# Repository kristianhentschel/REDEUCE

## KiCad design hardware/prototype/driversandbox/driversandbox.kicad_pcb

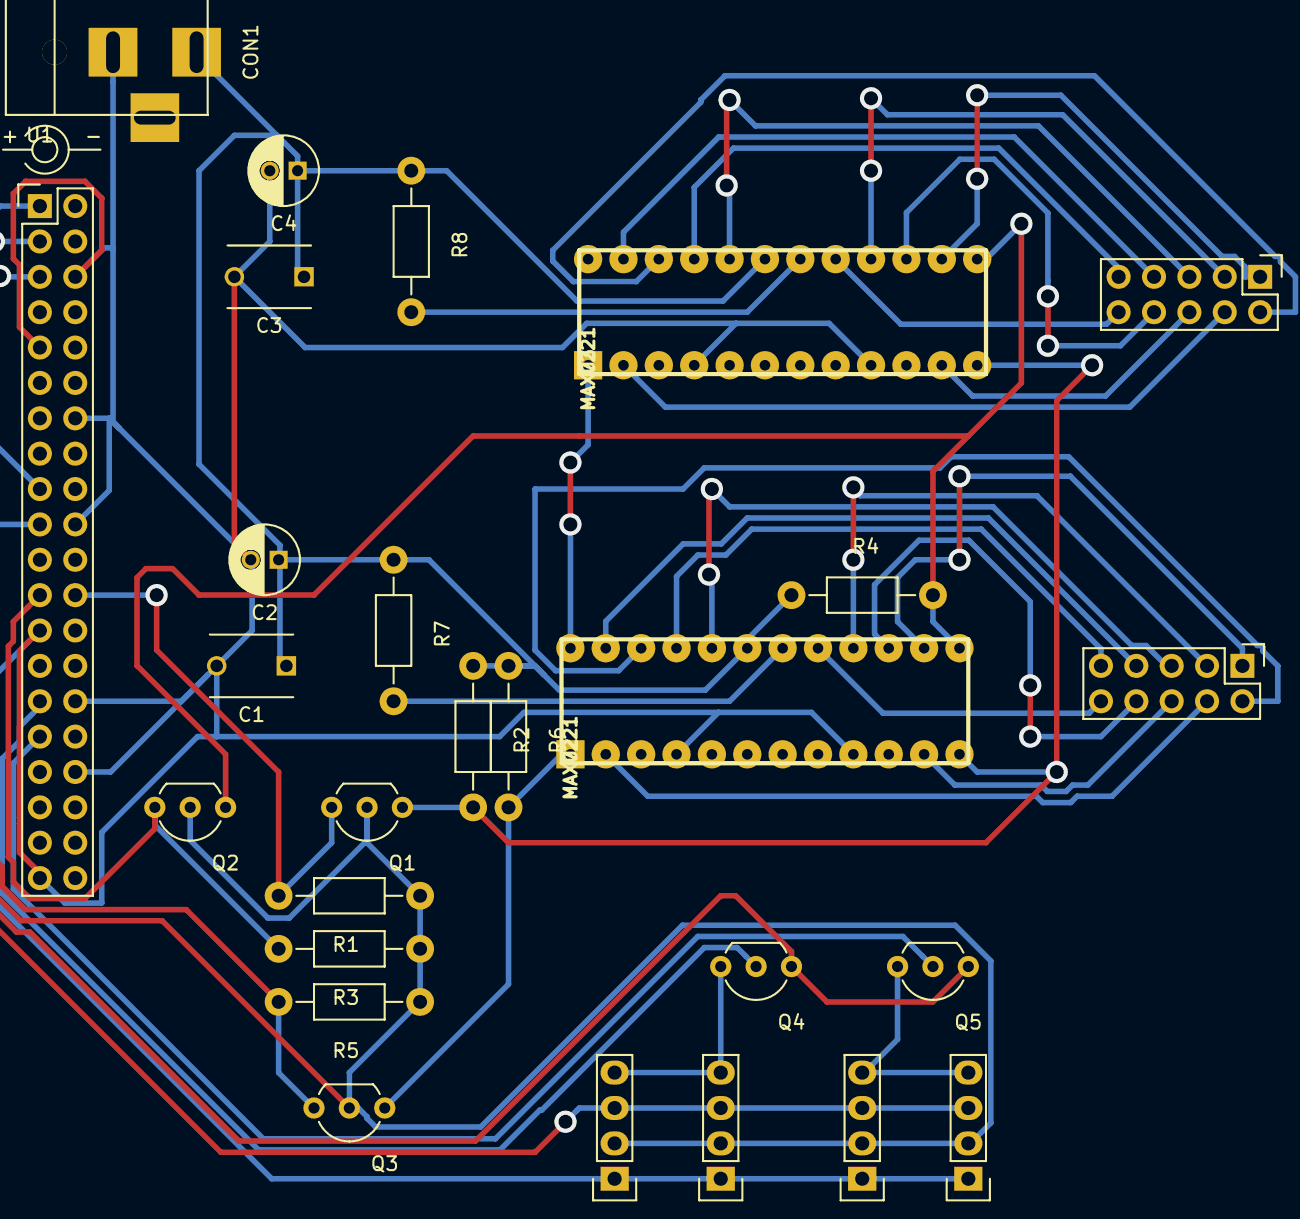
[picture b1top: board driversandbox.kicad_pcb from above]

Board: 2 copper layers, 27 parts (0 on the bottom side), 38 nets.

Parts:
C1, C3: C; C_Disc_D6_P5
C2, C4: CP; C_Radial_D5_L11_P2
CON1: BARREL_JACK; BARREL_JACK-custom
P1, P2, P3, P4: CONN_01X04; Pin_Header_Straight_1x04
P20, P24: CONN_02X05; Pin_Header_Straight_2x05
Q1, Q2, Q3, Q4, Q5: 2N7000; TO-92_Inline_Wide
R1, R2, R3, R4, R5, R6: 10K; Resistor_Horizontal_RM10mm
R7, R8: R_SET; Resistor_Horizontal_RM10mm
U1: Pi2_Connector; Pin_Header_Straight_2x20
U2, U3: MAX7221; DIL24

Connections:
/EN_I2C0_1: Q4.2, U1.29
/EN_I2C0_2: Q5.2, U1.31
/I2C1_SCL: Q4.1, Q5.1, U1.5
/I2C1_SDA: P1.3, P2.3, P3.3, P4.3, U1.3
/sheet57A5CF13/CLK_5V: Q2.1, R4.2, U2.13, U3.13
/sheet57A5CF13/DIG0: P20.4, U2.2
/sheet57A5CF13/DIG1: P20.6, U2.11
/sheet57A5CF13/SEGA: P20.1, U2.14
/sheet57A5CF13/SEGB: P20.3, U2.16
/sheet57A5CF13/SEGC: P20.5, U2.20
/sheet57A5CF13/SEGD: P20.7, U2.23
/sheet57A5CF13/SEGDP: P20.2, U2.22
/sheet57A5CF13/SEGE: P20.9, U2.21
/sheet57A5CF13/SEGF: P20.8, U2.15
/sheet57A5CF13/SEGG: P20.10, U2.17
/sheet57A5D898/DIG0: P24.4, U3.2
/sheet57A5D898/DIG1: P24.6, U3.11
/sheet57A5D898/DIN_5V: U2.24, U3.1
/sheet57A5D898/SEGA: P24.1, U3.14
/sheet57A5D898/SEGB: P24.3, U3.16
/sheet57A5D898/SEGC: P24.5, U3.20
/sheet57A5D898/SEGD: P24.7, U3.23
/sheet57A5D898/SEGDP: P24.2, U3.22
/sheet57A5D898/SEGE: P24.9, U3.21
/sheet57A5D898/SEGF: P24.8, U3.15
/sheet57A5D898/SEGG: P24.10, U3.17
/sheet57A33FA6/CMOS_OUT: Q1.1, R2.2, U2.12, U3.12
/sheet57A33FA6/TTL_IN: Q1.3, R1.2, U1.24
/sheet57A33FA7/TTL_IN: Q2.3, R3.2, U1.23
/sheet57A33FA8/CMOS_OUT: Q3.1, R6.2, U2.1
/sheet57A33FA8/TTL_IN: Q3.3, R5.2, U1.19
GND: C1.2, C2.2, C3.2, C4.2, CON1.2, P1.1, P2.1, P3.1, P4.1, U1.6, U1.9, U1.14, U1.20, U1.25, U1.30, U1.34, U1.39, U2.4, U2.9, U3.4, U3.9
unnamed: P1.4, P3.4, Q4.3
unnamed: P2.4, P4.4, Q5.3
unnamed: R7.2, U2.18
unnamed: R8.2, U3.18
VCC: C1.1, C2.1, C3.1, C4.1, CON1.1, R2.1, R4.1, R6.1, R7.1, R8.1, U2.19, U3.19
VDD: P1.2, P2.2, P3.2, P4.2, Q1.2, Q2.2, Q3.2, R1.1, R3.1, R5.1, U1.1, U1.17

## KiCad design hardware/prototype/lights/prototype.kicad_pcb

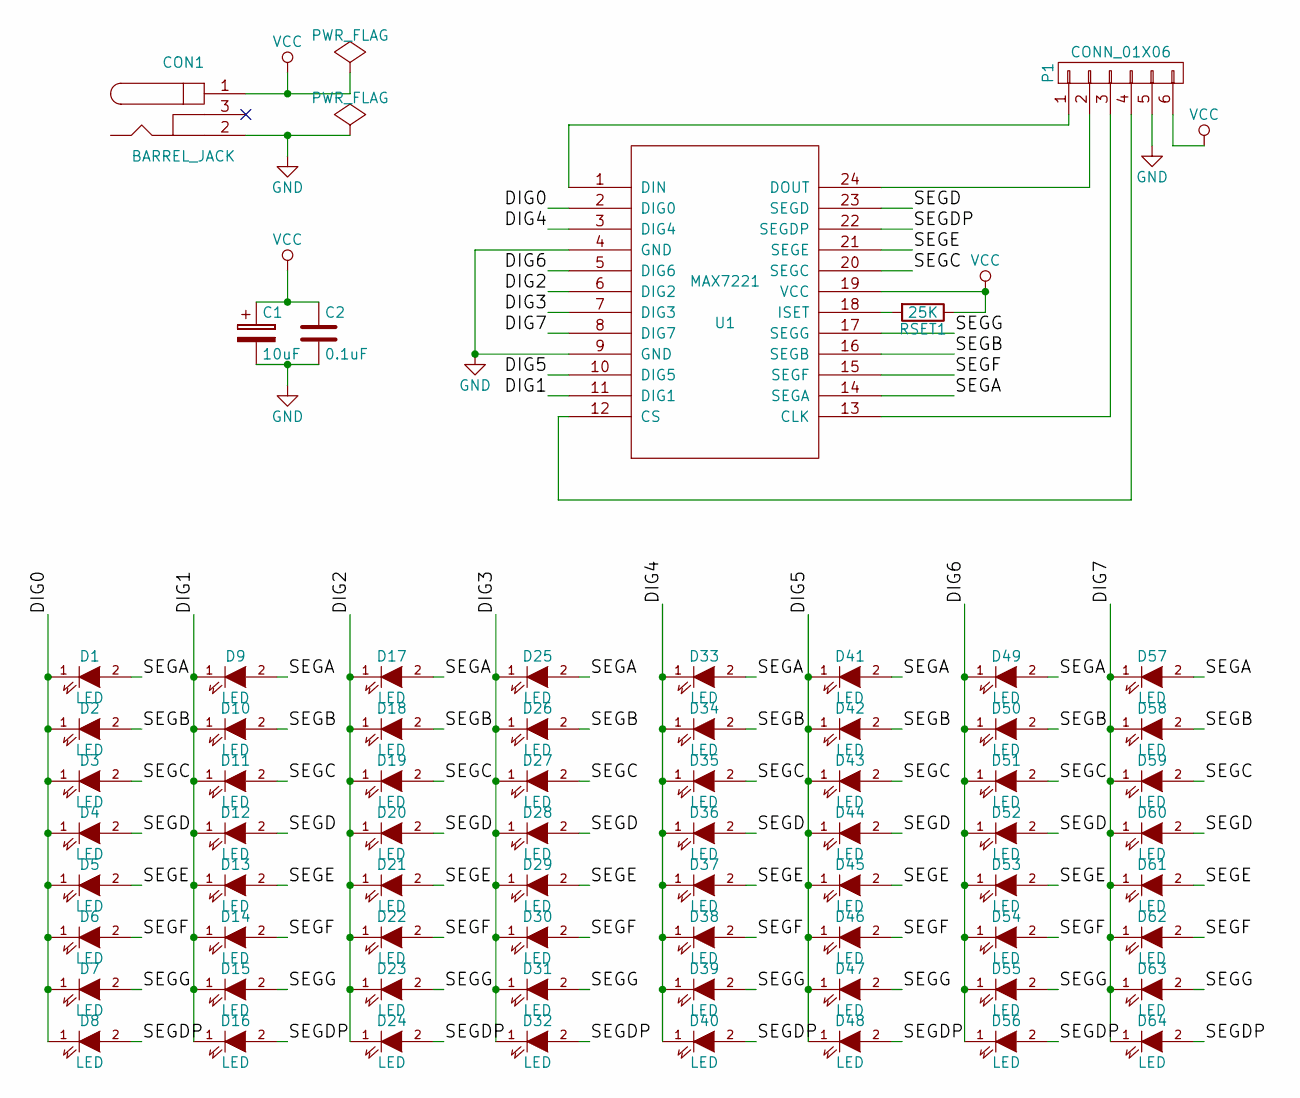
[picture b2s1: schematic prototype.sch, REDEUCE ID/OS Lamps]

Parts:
C1: 10uF
C2: 0.1uF
CON1: BARREL_JACK
D1, D2, D3, D4, D5, D6, D7, D8, D9, D10, D11, D12, D13, D14, D15, D16, D17, D18, D19, D20, D21, D22, D23, D24, D25, D26, D27, D28, D29, D30, D31, D32, D33, D34, D35, D36, D37, D38, D39, D40, D41, D42, D43, D44, D45, D46, D47, D48, D49, D50, D51, D52, D53, D54, D55, D56, D57, D58, D59, D60, D61, D62, D63, D64: LED; LED-5MM
P1: CONN_01X06; Pin_Header_Angled_1x06
RSET1: 25K; Resistor_Horizontal_RM10mm
U1: MAX7221; DIL24

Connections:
/DIG0: D1.1 (K), D2.1 (K), D3.1 (K), D4.1 (K), D5.1 (K), D6.1 (K), D7.1 (K), D8.1 (K), U1.2 (DIG0)
/DIG1: D9.1 (K), D10.1 (K), D11.1 (K), D12.1 (K), D13.1 (K), D14.1 (K), D15.1 (K), D16.1 (K), U1.11 (DIG1)
/DIG2: D17.1 (K), D18.1 (K), D19.1 (K), D20.1 (K), D21.1 (K), D22.1 (K), D23.1 (K), D24.1 (K), U1.6 (DIG2)
/DIG3: D25.1 (K), D26.1 (K), D27.1 (K), D28.1 (K), D29.1 (K), D30.1 (K), D31.1 (K), D32.1 (K), U1.7 (DIG3)
/DIG4: D33.1 (K), D34.1 (K), D35.1 (K), D36.1 (K), D37.1 (K), D38.1 (K), D39.1 (K), D40.1 (K), U1.3 (DIG4)
/DIG5: D41.1 (K), D42.1 (K), D43.1 (K), D44.1 (K), D45.1 (K), D46.1 (K), D47.1 (K), D48.1 (K), U1.10 (DIG5)
/DIG6: D49.1 (K), D50.1 (K), D51.1 (K), D52.1 (K), D53.1 (K), D54.1 (K), D55.1 (K), D56.1 (K), U1.5 (DIG6)
/DIG7: D57.1 (K), D58.1 (K), D59.1 (K), D60.1 (K), D61.1 (K), D62.1 (K), D63.1 (K), D64.1 (K), U1.8 (DIG7)
/SEGA: D1.2 (A), D9.2 (A), D17.2 (A), D25.2 (A), D33.2 (A), D41.2 (A), D49.2 (A), D57.2 (A), U1.14 (SEGA)
/SEGB: D2.2 (A), D10.2 (A), D18.2 (A), D26.2 (A), D34.2 (A), D42.2 (A), D50.2 (A), D58.2 (A), U1.16 (SEGB)
/SEGC: D3.2 (A), D11.2 (A), D19.2 (A), D27.2 (A), D35.2 (A), D43.2 (A), D51.2 (A), D59.2 (A), U1.20 (SEGC)
/SEGD: D4.2 (A), D12.2 (A), D20.2 (A), D28.2 (A), D36.2 (A), D44.2 (A), D52.2 (A), D60.2 (A), U1.23 (SEGD)
/SEGDP: D8.2 (A), D16.2 (A), D24.2 (A), D32.2 (A), D40.2 (A), D48.2 (A), D56.2 (A), D64.2 (A), U1.22 (SEGDP)
/SEGE: D5.2 (A), D13.2 (A), D21.2 (A), D29.2 (A), D37.2 (A), D45.2 (A), D53.2 (A), D61.2 (A), U1.21 (SEGE)
/SEGF: D6.2 (A), D14.2 (A), D22.2 (A), D30.2 (A), D38.2 (A), D46.2 (A), D54.2 (A), D62.2 (A), U1.15 (SEGF)
/SEGG: D7.2 (A), D15.2 (A), D23.2 (A), D31.2 (A), D39.2 (A), D47.2 (A), D55.2 (A), D63.2 (A), U1.17 (SEGG)
GND: C1.2, C2.2, CON1.2, P1.5, U1.4 (GND), U1.9 (GND)
unnamed: P1.1, U1.1 (DIN)
unnamed: P1.2, U1.24 (DOUT)
unnamed: P1.3, U1.13 (CLK)
unnamed: P1.4, U1.12 (CS)
unnamed: RSET1.2, U1.18 (ISET)
VCC: C1.1, C2.1, CON1.1, P1.6, RSET1.1, U1.19 (VCC)

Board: 2 copper layers, 68 parts (0 on the bottom side), 23 nets, no tracks yet.

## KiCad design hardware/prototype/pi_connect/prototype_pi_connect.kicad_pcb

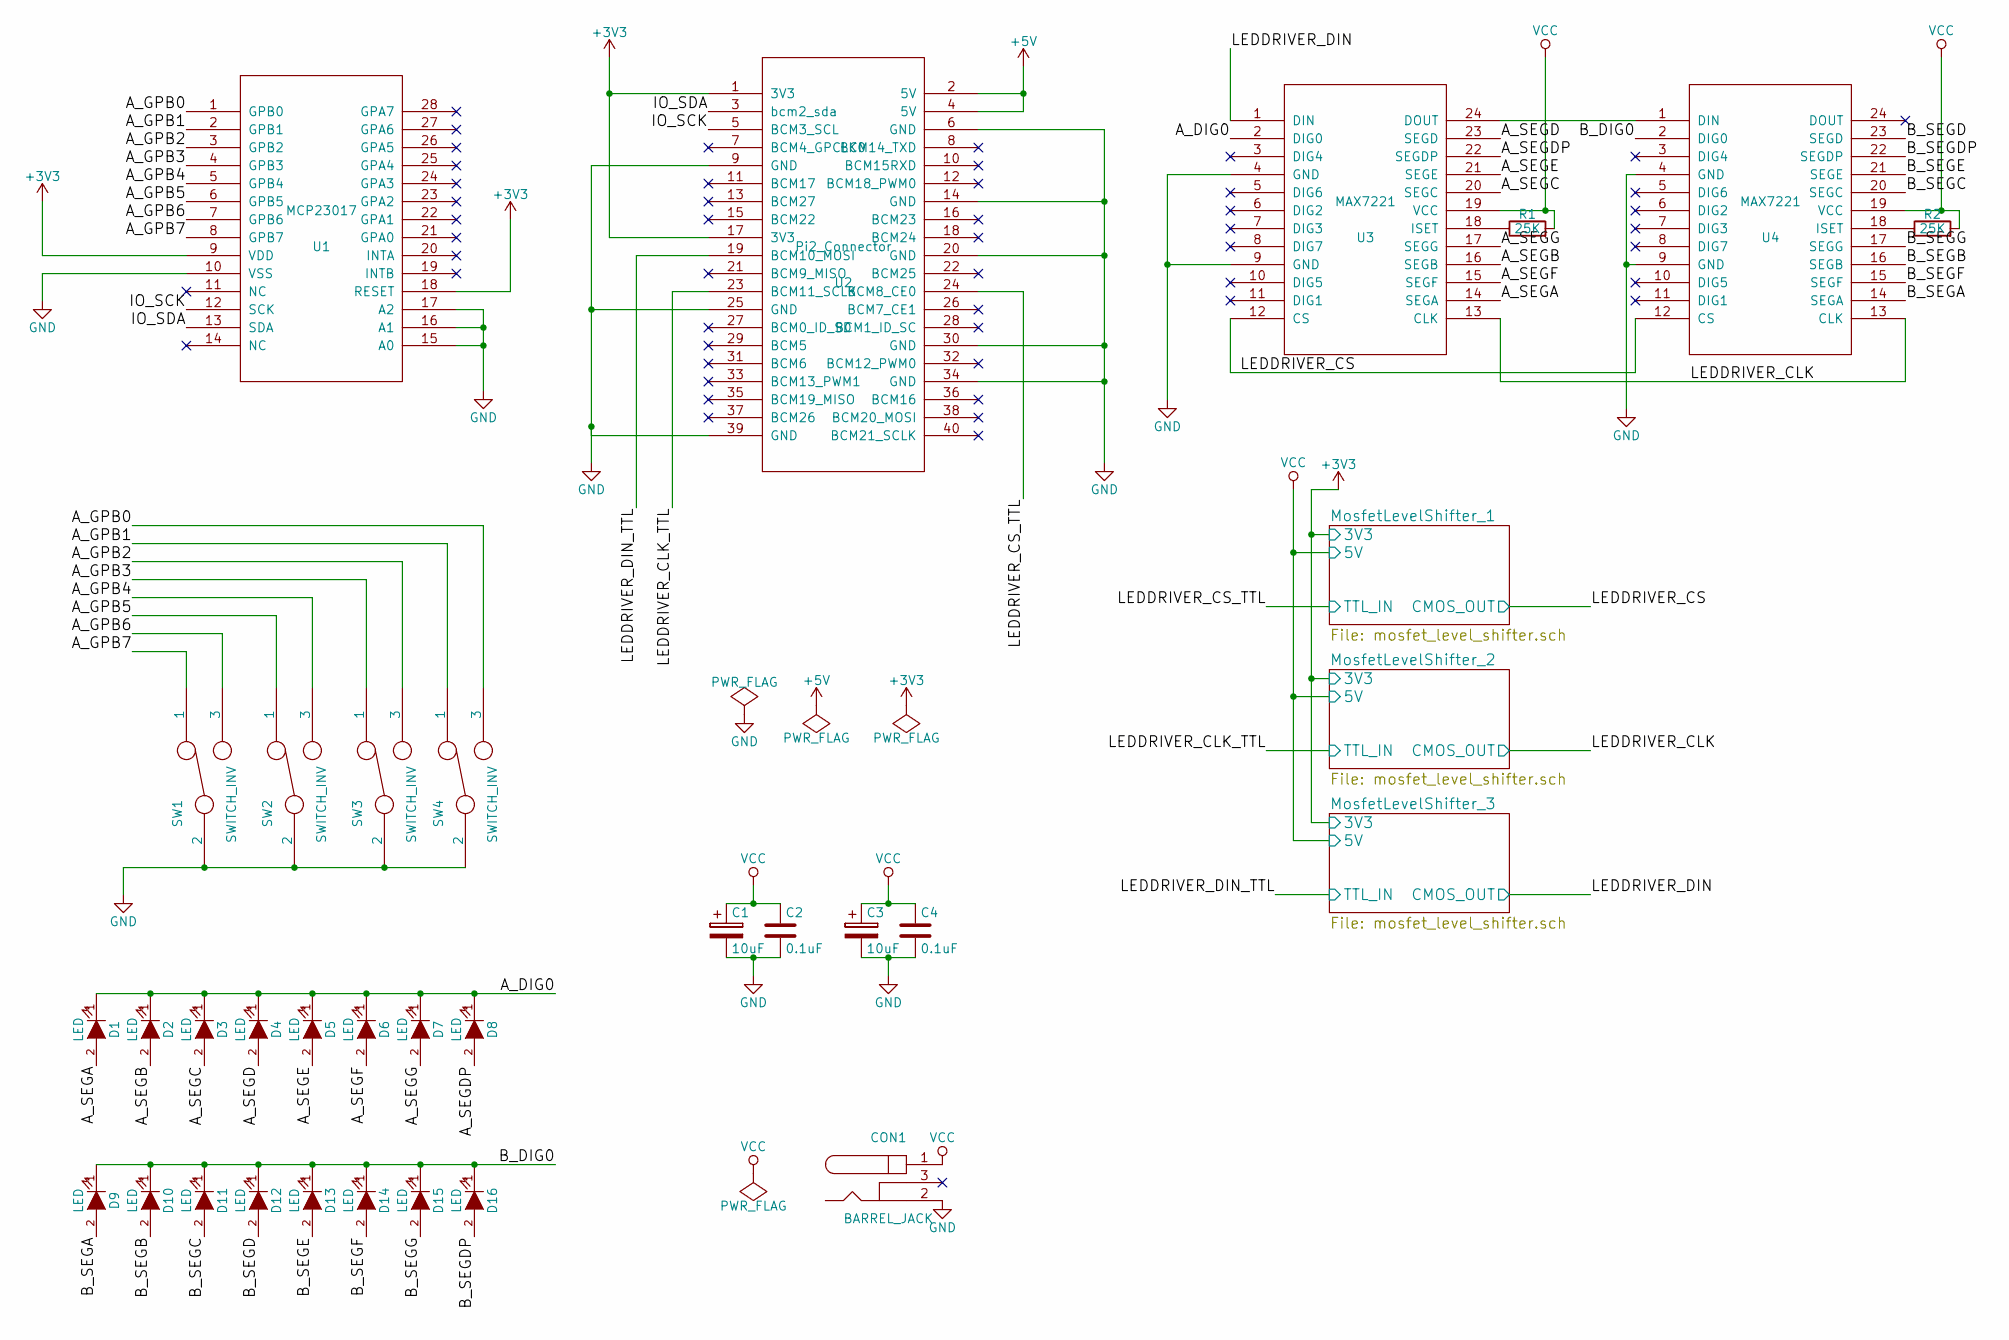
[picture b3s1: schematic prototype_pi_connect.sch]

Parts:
C1, C3: 10uF; CP5
C2, C4: 0.1uF; C_Disc_D6_P5
CON1: BARREL_JACK
D1, D2, D3, D4, D5, D6, D7, D8, D9, D10, D11, D12, D13, D14, D15, D16: LED; LED-5MM
R1, R2: 25K; Resistor_Horizontal_RM10mm
SW1, SW2, SW3, SW4: SWITCH_INV; SW_SPDT
U1: MCP23017; DIL28
U2: Pi2_Connector; CONN_02x20
U3, U4: MAX7221; DIL24

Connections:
+3V3: U1.9 (VDD), U1.18 (RESET), U2.1 (3V3), U2.17 (3V3); also elsewhere on the board
+5V: U2.2 (5V), U2.4 (5V)
/A_DIG0: D1.1 (K), D2.1 (K), D3.1 (K), D4.1 (K), D5.1 (K), D6.1 (K), D7.1 (K), D8.1 (K), U3.2 (DIG0)
/A_GPB0: SW4.3, U1.1 (GPB0)
/A_GPB1: SW4.1, U1.2 (GPB1)
/A_GPB2: SW3.3, U1.3 (GPB2)
/A_GPB3: SW3.1, U1.4 (GPB3)
/A_GPB4: SW2.3, U1.5 (GPB4)
/A_GPB5: SW2.1, U1.6 (GPB5)
/A_GPB6: SW1.3, U1.7 (GPB6)
/A_GPB7: SW1.1, U1.8 (GPB7)
/A_SEGA: D1.2 (A), U3.14 (SEGA)
/A_SEGB: D2.2 (A), U3.16 (SEGB)
/A_SEGC: D3.2 (A), U3.20 (SEGC)
/A_SEGD: D4.2 (A), U3.23 (SEGD)
/A_SEGDP: D8.2 (A), U3.22 (SEGDP)
/A_SEGE: D5.2 (A), U3.21 (SEGE)
/A_SEGF: D6.2 (A), U3.15 (SEGF)
/A_SEGG: D7.2 (A), U3.17 (SEGG)
/B_DIG0: D9.1 (K), D10.1 (K), D11.1 (K), D12.1 (K), D13.1 (K), D14.1 (K), D15.1 (K), D16.1 (K), U4.2 (DIG0)
/B_SEGA: D9.2 (A), U4.14 (SEGA)
/B_SEGB: D10.2 (A), U4.16 (SEGB)
/B_SEGC: D11.2 (A), U4.20 (SEGC)
/B_SEGD: D12.2 (A), U4.23 (SEGD)
/B_SEGDP: D16.2 (A), U4.22 (SEGDP)
/B_SEGE: D13.2 (A), U4.21 (SEGE)
/B_SEGF: D14.2 (A), U4.15 (SEGF)
/B_SEGG: D15.2 (A), U4.17 (SEGG)
/IO_SCK: U1.12 (SCK), U2.5 (BCM3_SCL)
/IO_SDA: U1.13 (SDA), U2.3 (bcm2_sda)
/LEDDRIVER_CLK: U3.13 (CLK), U4.13 (CLK); also elsewhere on the board
/LEDDRIVER_CLK_TTL: U2.23 (BCM11_SCLK); also elsewhere on the board
/LEDDRIVER_CS: U3.12 (CS), U4.12 (CS); also elsewhere on the board
/LEDDRIVER_CS_TTL: U2.24 (BCM8_CE0); also elsewhere on the board
/LEDDRIVER_DIN: U3.1 (DIN); also elsewhere on the board
/LEDDRIVER_DIN_TTL: U2.19 (BCM10_MOSI); also elsewhere on the board
GND: C1.2, C2.2, C3.2, C4.2, CON1.2, SW1.2, SW2.2, SW3.2, SW4.2, U1.10 (VSS), U1.15 (A0), U1.16 (A1), U1.17 (A2), U2.6 (GND), U2.9 (GND), U2.14 (GND), U2.20 (GND), U2.25 (GND), U2.30 (GND), U2.34 (GND), U2.39 (GND), U3.4 (GND), U3.9 (GND), U4.4 (GND), U4.9 (GND)
unnamed: R1.1, U3.18 (ISET)
unnamed: R2.1, U4.18 (ISET)
unnamed: U3.24 (DOUT), U4.1 (DIN)
VCC: C1.1, C2.1, C3.1, C4.1, CON1.1, R1.2, R2.2, U3.19 (VCC), U4.19 (VCC); also elsewhere on the board

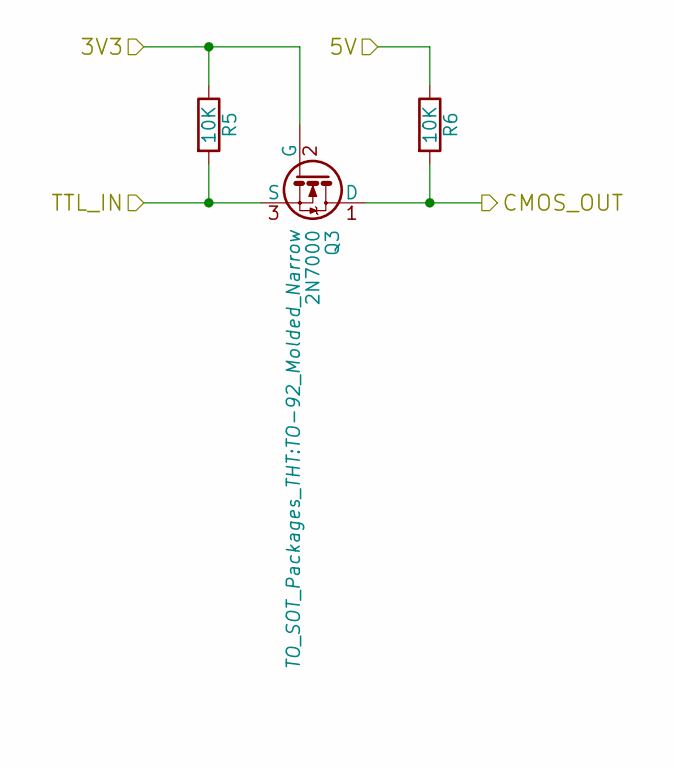
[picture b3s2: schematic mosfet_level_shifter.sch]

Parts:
Q1: 2N7000; TO-92_Molded_Narrow
R3, R4: 10K; Resistor_Horizontal_RM10mm

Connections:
+3V3: Q1.2 (G), R3.1; also elsewhere on the board
/LEDDRIVER_CS: Q1.1 (D), R4.2; also elsewhere on the board
/LEDDRIVER_CS_TTL: Q1.3 (S), R3.2; also elsewhere on the board
VCC: R4.1; also elsewhere on the board

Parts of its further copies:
Q2, Q3: 2N7000; TO-92_Molded_Narrow
R5, R6, R7, R8: 10K; Resistor_Horizontal_RM10mm

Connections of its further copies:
+3V3: Q2.2 (G), Q3.2 (G), R5.1, R7.1; also elsewhere on the board
/LEDDRIVER_CLK: Q2.1 (D), R8.2; also elsewhere on the board
/LEDDRIVER_CLK_TTL: Q2.3 (S), R7.2; also elsewhere on the board
/LEDDRIVER_DIN: Q3.1 (D), R6.2; also elsewhere on the board
/LEDDRIVER_DIN_TTL: Q3.3 (S), R5.2; also elsewhere on the board
VCC: R6.1, R8.1; also elsewhere on the board

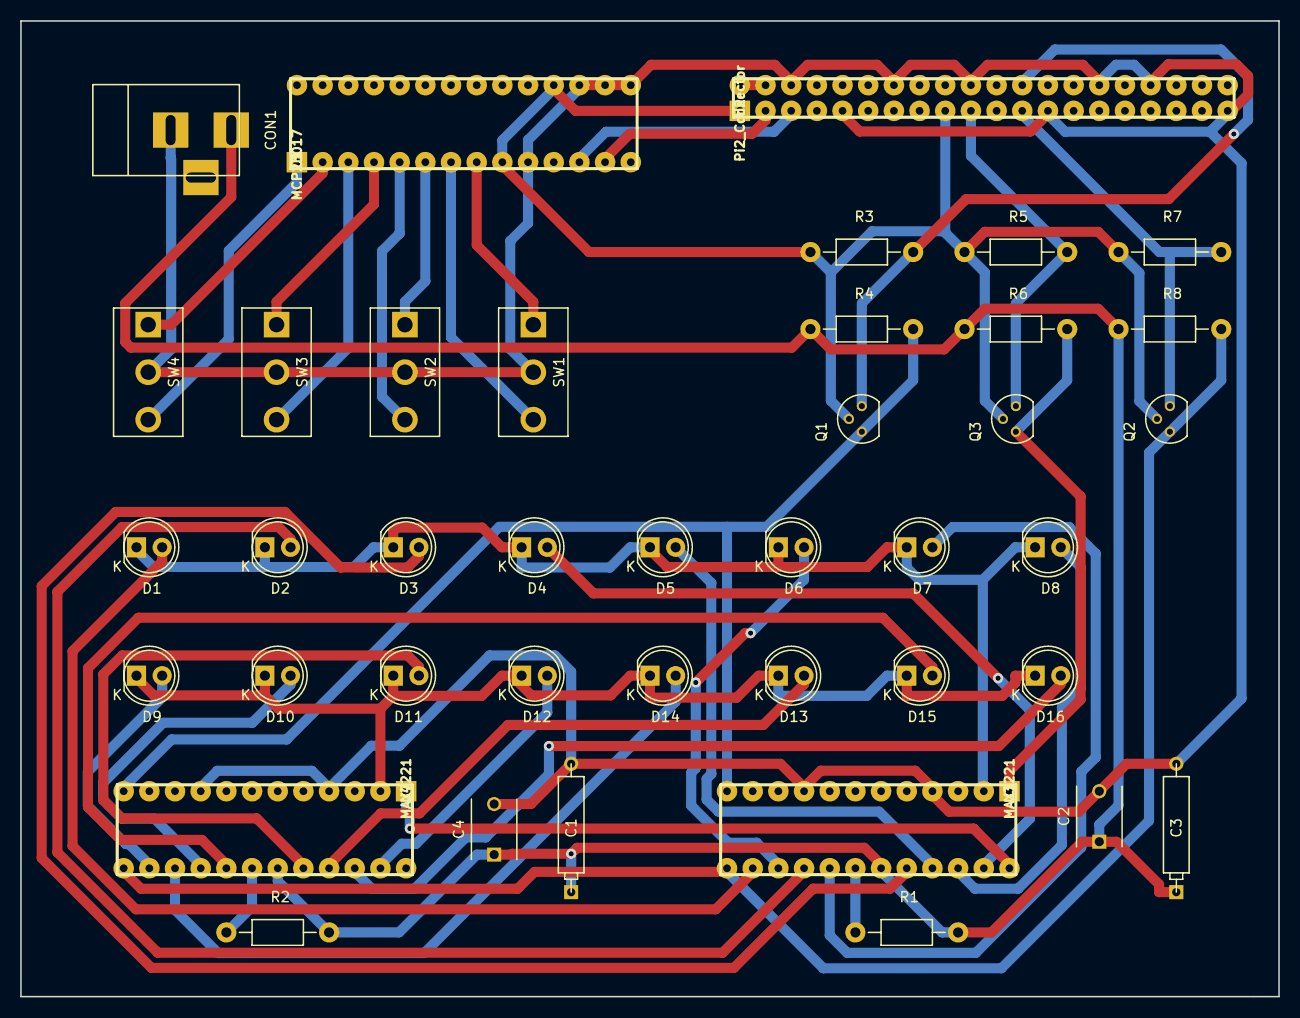
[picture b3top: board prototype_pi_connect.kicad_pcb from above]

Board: 2 copper layers, 124.5 x 96.5 mm, 40 parts (0 on the bottom side), 41 nets.

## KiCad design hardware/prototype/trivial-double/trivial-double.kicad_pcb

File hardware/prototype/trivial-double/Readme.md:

# Components placement

Switch and LED 'front', connected on back copper layer.

Resistor and Connector 'back', connected on front copper layer (one resistor leg on back copper).

# Design Rules

- Minimum Hole diameter 1.0 (default)
- Via Dia 1.5 - Via Drill 1.0
- Minimum track width 0.5
- Clearance 0.4

## Previous version, as produced 
- Minimum Hole diameter 0.3 (default)
- Via Dia 0.6 - Via Drill 0.3
- Minimum track width 0.4
- Clearance 0.4

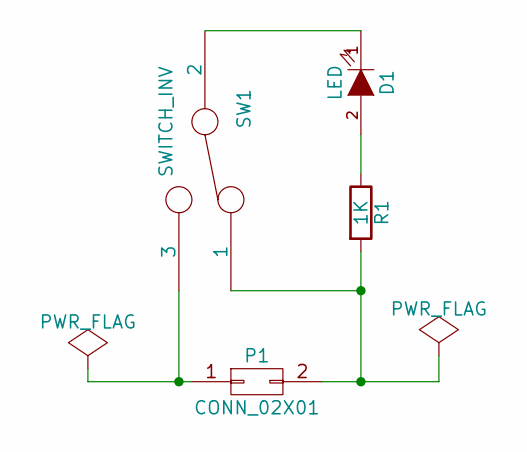
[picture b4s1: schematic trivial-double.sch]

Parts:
D1: LED; LED-5MM
P1: CONN_02X01; Pin_Header_Straight_2x01
R1: 1K; Resistor_Horizontal_RM10mm
SW1: SWITCH_INV; SW_SPDT

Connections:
unnamed: D1.1 (K), SW1.2
unnamed: D1.2 (A), R1.1
unnamed: P1.1, SW1.3
unnamed: P1.2, R1.2, SW1.1

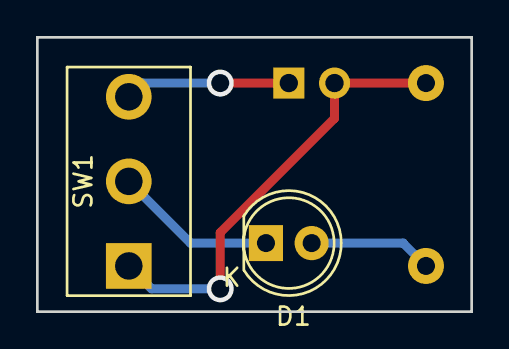
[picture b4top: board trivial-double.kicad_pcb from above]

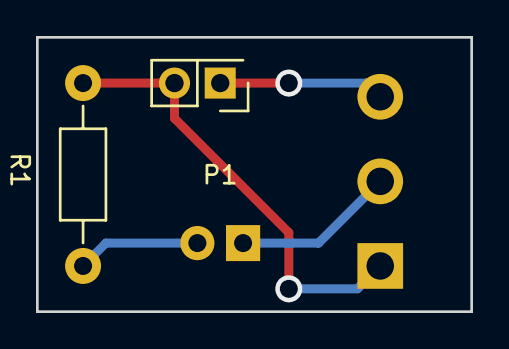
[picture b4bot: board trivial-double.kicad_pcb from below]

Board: 2 copper layers, 24.1 x 15.2 mm, 4 parts (2 on the bottom side), 4 nets.

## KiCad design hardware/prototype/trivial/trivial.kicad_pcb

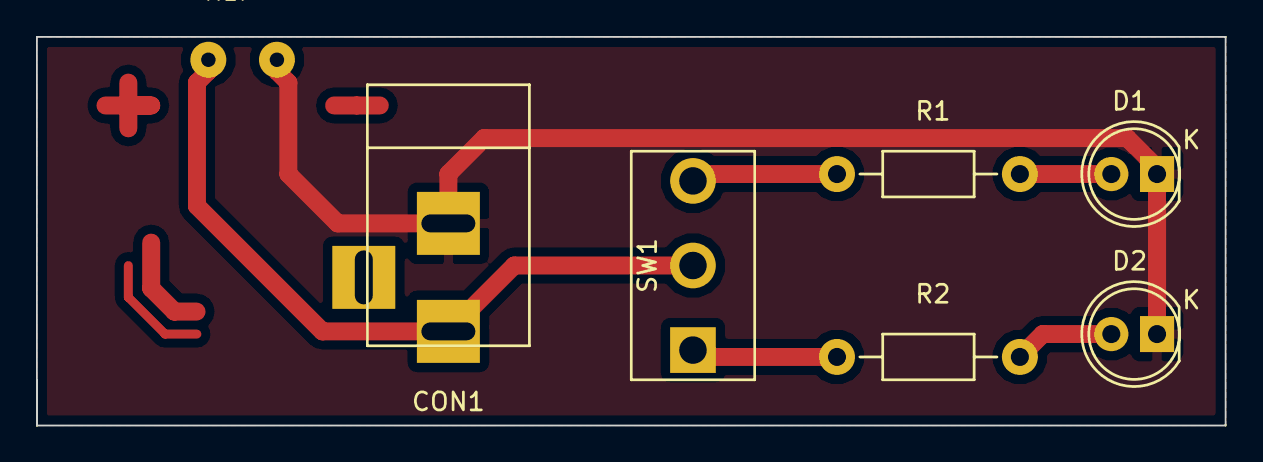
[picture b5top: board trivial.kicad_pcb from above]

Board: 2 copper layers, 66.0 x 21.6 mm, 6 parts (0 on the bottom side), 6 nets.

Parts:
CON1: BARREL_JACK
D1, D2: LED; LED-5MM
R1, R2: R; Resistor_Horizontal_RM10mm
SW1: SWITCH_INV; SW_SPDT

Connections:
unnamed: CON1.1, SW1.2
unnamed: CON1.2, D1.1, D2.1
unnamed: D1.2, R1.2
unnamed: D2.2, R2.2
unnamed: R1.1, SW1.3
unnamed: R2.1, SW1.1

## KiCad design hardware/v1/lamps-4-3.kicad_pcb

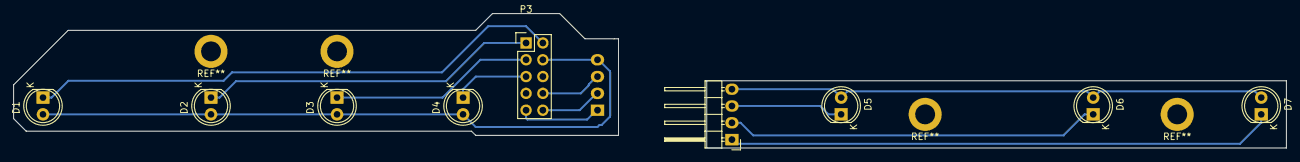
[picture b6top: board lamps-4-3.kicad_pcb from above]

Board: 2 copper layers, 192.4 x 20.3 mm, 10 parts (1 on the bottom side), 12 nets.

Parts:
D1, D2, D3, D4, D5, D6, D7: LED; LED-5MM-custom
P1, P2: CONN_01X04; Pin_Header_Angled_1x04
P3: CONN_02X05; Pin_Header_Straight_2x05

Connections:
/DIGITA: D1.2, D2.2, D3.2, D4.2, P1.4, P3.4
/SEG0: D1.1, P3.2
/SEG1: D2.1, P3.1
/SEG2: D3.1, P3.3
/SEG3: D4.1, P3.5
/SEG5: P1.1, P3.9
/SEG6: P1.2, P3.10
/SEG7: P1.3, P3.8
unnamed: D5.1, P2.3
unnamed: D5.2, D6.2, D7.2, P2.4
unnamed: D6.1, P2.2
unnamed: D7.1, P2.1
